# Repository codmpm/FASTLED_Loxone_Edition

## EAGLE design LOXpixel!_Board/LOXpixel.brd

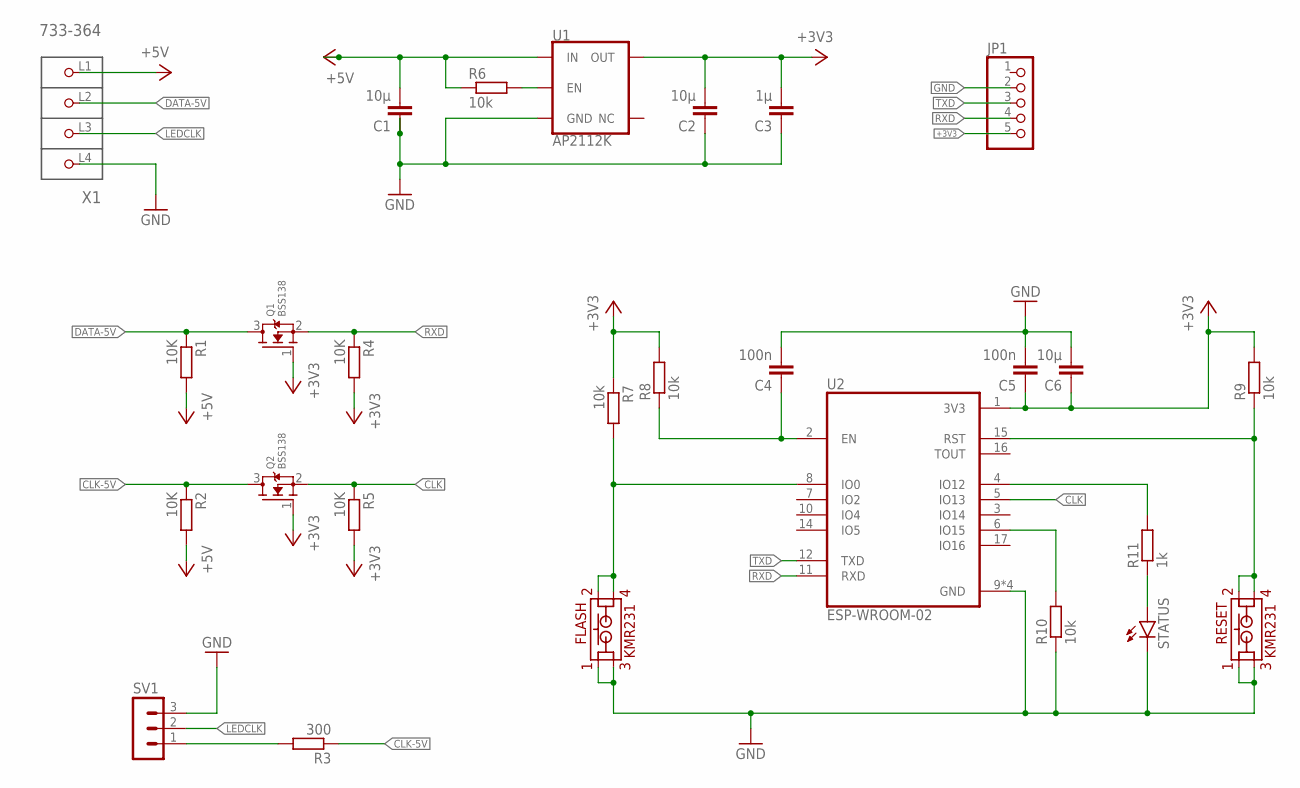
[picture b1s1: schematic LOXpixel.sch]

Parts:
C1, C2, C6: 10µ; C0805
C3: 1µ; C0805
C4, C5: 100n; C0805
FLASH: KMR231; GLFS
JP1: PINHD-1X5; 1X05
Q1, Q2: BSS138; SOT23
R1, R2, R4, R5: 10K; R0805
R3: 300; R0805
R6, R7, R8, R9, R10: 10k; R0805
R11: 1k; R0805
RESET: KMR231; GLFS
STATUS: LEDCHIPLED_0805; CHIPLED_0805
SV1: MA03-1
U1: AP2112K; SOT23-5
U2: ESP-WROOM-02; MODULE_ESP-WROOM-02
X1: 733-364; P-733-364

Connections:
+3V3: C2.2, C3.2, C5.1, C6.1, JP1.5, Q1.1 (G), Q2.1 (G), R4.2, R5.2, R7.1, R8.2, R9.2, U1.5 (OUT), U2.1 (3V3)
+5V: C1.2, R1.2, R2.2, R6.1, U1.1 (IN), X1.L1 (P1)
BOOTMODE: R10.2, U2.6 (IO15)
CHIPEN: C4.1, R8.1, U2.2 (EN)
CLK: Q2.2 (S), R5.1, U2.5 (IO13)
CLK-5V: Q2.3 (D), R2.1, R3.1
DATA-5V: Q1.3 (D), R1.1, X1.L2 (P2)
FLASH: FLASH.P$2 (2), FLASH.P$4 (4), R7.2, U2.8 (IO0)
GND: C1.1, C2.1, C3.1, C4.2, C5.2, C6.2, FLASH.P$1 (1), FLASH.P$3 (3), JP1.2, R10.1, RESET.P$1 (1), RESET.P$3 (3), STATUS.C, SV1.3, U1.2 (GND), U2.9 (GND), U2.13 (GND), U2.18 (GND), U2.19 (GND), X1.L4 (P4)
LEDCLK: SV1.2, X1.L3 (P3)
unnamed: R6.2, U1.3 (EN)
unnamed: R11.1, STATUS.A
unnamed: R3.2, SV1.1
RST: R9.1, RESET.P$2 (2), RESET.P$4 (4), U2.15 (RST)
RXD: JP1.4, Q1.2 (S), R4.1, U2.11 (RXD)
STATLED: R11.2, U2.4 (IO12)
TXD: JP1.3, U2.12 (TXD)

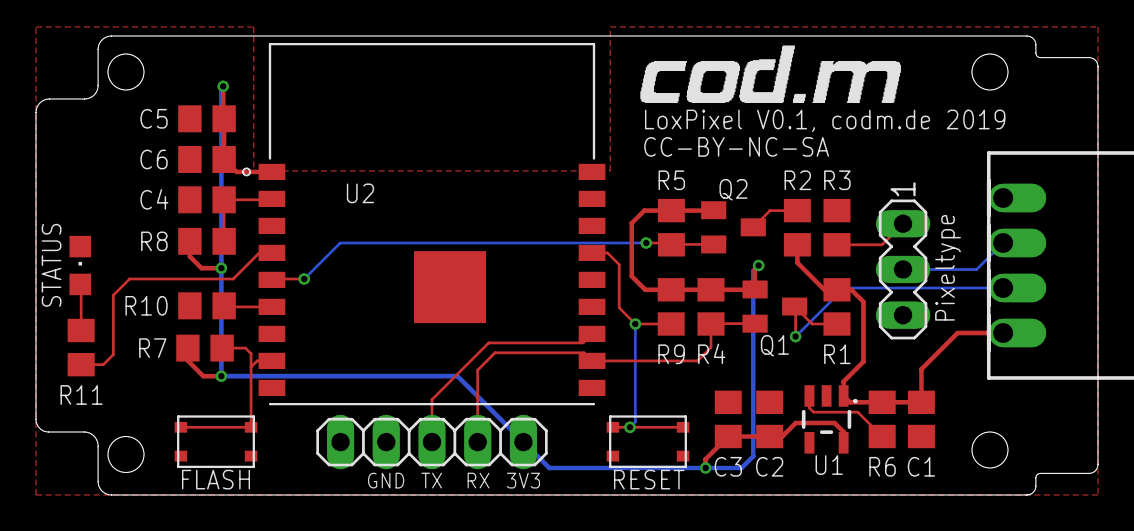
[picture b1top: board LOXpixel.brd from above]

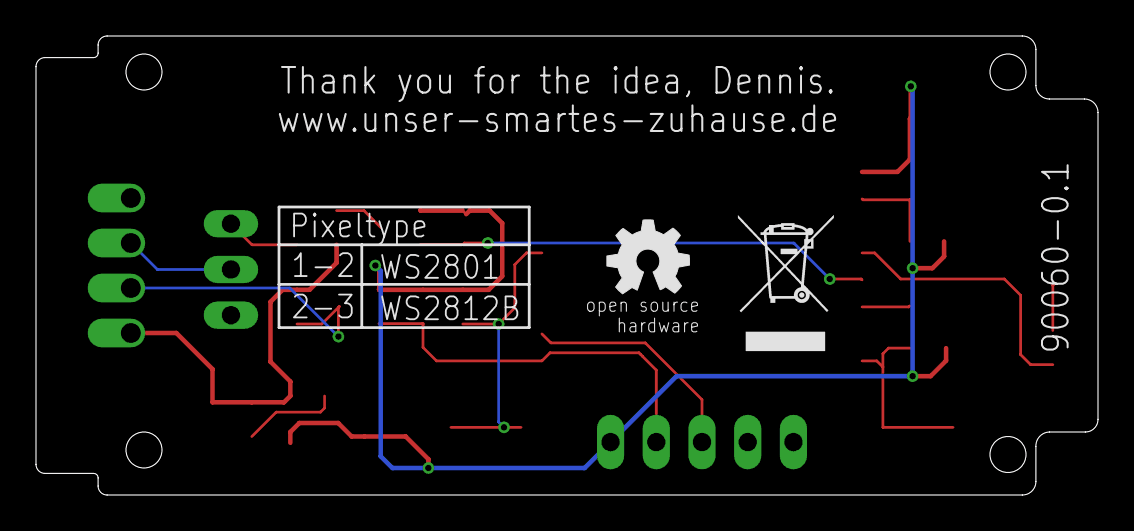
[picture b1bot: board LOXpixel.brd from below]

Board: 2 copper layers, 59.0 x 25.5 mm, 30 parts (2 on the bottom side), 17 nets.

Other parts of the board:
U$1: CODM-LOGO
U$2: WEEE-LOGO-5MM
U$3: OSHW_5MM

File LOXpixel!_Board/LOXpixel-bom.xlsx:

| LoxPixel V0.1
 | Qty | Value | Device | Package | Parts | Description
 | 1 |  | LEDCHIPLED_0805 | CHIPLED_0805 | STATUS | LED
 | 1 |  | MA03-1 | MA03-1 | SV1 | PIN HEADER
 | 1 |  | PINHD-1X5 | 1X05 | JP1 | PIN HEADER
 | 2 | 100n | C-EUC0805 | C0805 | C4, C5 | CAPACITOR, European symbol
 | 4 | 10K | R-EU_R0805 | R0805 | R1, R2, R4, R5 | RESISTOR, European symbol
 | 5 | 10k | R-EU_R0805 | R0805 | R6, R7, R8, R9, R10 | RESISTOR, European symbol
 | 3 | 10µ | C-EUC0805 | C0805 | C1, C2, C6 | CAPACITOR, European symbol
 | 1 | 1k | R-EU_R0805 | R0805 | R11 | RESISTOR, European symbol
 | 1 | 1µ | C-EUC0805 | C0805 | C3 | CAPACITOR, European symbol
 | 1 | 300 | R-EU_R0805 | R0805 | R3 | RESISTOR, European symbol
 | 1 | 733-364 | 733-364 | P-733-364 | X1 | Serie 733, Stiftleiste (für Leiterplatten) Einlötstift abgewinkelt 0,8 x 0,8 mm
 | 1 | AP2112K | V_REG_AP2112K-3.3V | SOT23-5 | U1 | AP2112 - 600mA CMOS LDO Regulator w/ Enable
 | 2 | BSS138 | MOSFET-NREFLOW | SOT23 | Q1, Q2 | N-Channel Mosfet
 | 1 | ESP-WROOM-02 | ESP-WROOM-02 | MODULE_ESP-WROOM-02 | U2 | Wi-Fi Module w/ESP8266 802.11b/g/n 20dBm 20x18x3mm
 | 2 | KMR231 | KMR231 | GLFS | FLASH, RESET | Surface-mount Tactile Switch - Single-Pole, Single-Throw (SPST)

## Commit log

2019-10-24 pcb for hammond 1551usb3 and rebuild without nodemcu and for esp-wroom-02
2019-10-28 finished first board revision
2019-11-19 added bom

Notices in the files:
LOXpixel!_Board/LOXpixel.brd:
CC-BY-NC-SA
parts and their libraries:
SparkFun-IC-Power: Licensing: Creative Commons ShareAlike 4.0 International - https://creativecommons.org/licenses/by-sa/4.0
